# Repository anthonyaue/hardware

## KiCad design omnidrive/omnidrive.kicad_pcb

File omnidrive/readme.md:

List of components for digikey at https://www.digikey.com/en/mylists/list/IZ52OHNOLU

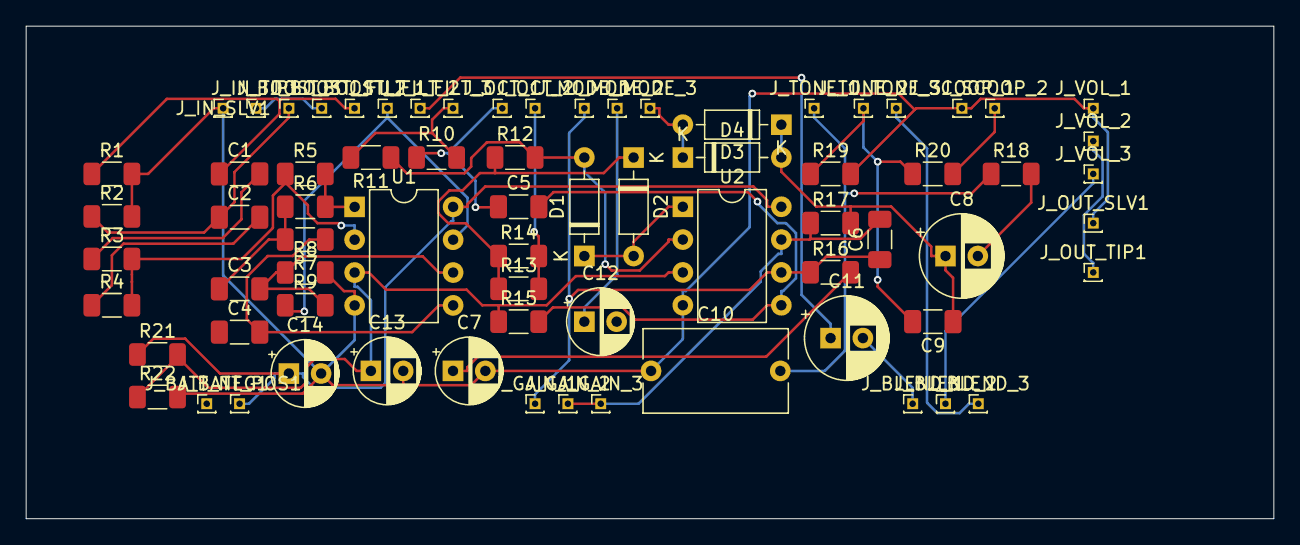
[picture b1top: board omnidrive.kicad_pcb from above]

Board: 2 copper layers, 96.5 x 38.1 mm, 73 parts (0 on the bottom side), 36 nets.

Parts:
C1, C5: 0.01uF; C_1206_3216Metric_Pad1.33x1.80mm_HandSolder
C2, C3, C4: 0.001uF; C_1206_3216Metric_Pad1.33x1.80mm_HandSolder
C6: 47pF; C_1206_3216Metric_Pad1.33x1.80mm_HandSolder
C7, C12, C13, C14: 10uF; CP_Radial_D5.0mm_P2.50mm
C8, C11: 1uF; CP_Radial_D6.3mm_P2.50mm
C9: 0.047uF; C_1206_3216Metric_Pad1.33x1.80mm_HandSolder
C10: 0.1uF; C_Rect_L11.0mm_W6.3mm_P10.00mm_MKT
D1, D2, D3, D4: 1N914; D_DO-35_SOD27_P7.62mm_Horizontal
J_BATT_NEG1: Conn_01x01_Pin; PinHeader_1x01_P1.00mm_Vertical
J_BATT_POS1: Conn_01x01_Pin; PinHeader_1x01_P1.00mm_Vertical
J_BLEND_1, J_BLEND_2, J_BLEND_3: Conn_01x01_Pin; PinHeader_1x01_P1.00mm_Vertical
J_BOOST_1, J_BOOST_2, J_BOOST_3: Conn_01x01_Pin; PinHeader_1x01_P1.00mm_Vertical
J_FILT_1, J_FILT_2, J_FILT_3: Conn_01x01_Pin; PinHeader_1x01_P1.00mm_Vertical
J_GAIN_1, J_GAIN_2, J_GAIN_3: Conn_01x01_Pin; PinHeader_1x01_P1.00mm_Vertical
J_IN_SLV1: Conn_01x01_Pin; PinHeader_1x01_P1.00mm_Vertical
J_IN_TIP1: Conn_01x01_Pin; PinHeader_1x01_P1.00mm_Vertical
J_MODE_1, J_MODE_2, J_MODE_3: Conn_01x01_Pin; PinHeader_1x01_P1.00mm_Vertical
J_OCT_1, J_OCT_2: Conn_01x01_Pin; PinHeader_1x01_P1.00mm_Vertical
J_OUT_SLV1: Conn_01x01_Pin; PinHeader_1x01_P1.00mm_Vertical
J_OUT_TIP1: Conn_01x01_Pin; PinHeader_1x01_P1.00mm_Vertical
J_SCOOP_1, J_SCOOP_2: Conn_01x01_Pin; PinHeader_1x01_P1.00mm_Vertical
J_TONE_1, J_TONE_2, J_TONE_3: Conn_01x01_Pin; PinHeader_1x01_P1.00mm_Vertical
J_VOL_1, J_VOL_2, J_VOL_3: Conn_01x01_Pin; PinHeader_1x01_P1.00mm_Vertical
R1, R2: 10M; R_1206_3216Metric_Pad1.30x1.75mm_HandSolder
R3: 330K; R_1206_3216Metric_Pad1.30x1.75mm_HandSolder
R4, R8, R9, R15: 100K; R_1206_3216Metric_Pad1.30x1.75mm_HandSolder
R5: 1M; R_1206_3216Metric_Pad1.30x1.75mm_HandSolder
R6, R7: 220K; R_1206_3216Metric_Pad1.30x1.75mm_HandSolder
R10, R11, R12, R13, R14, R19, R21, R22: 10K; R_1206_3216Metric_Pad1.30x1.75mm_HandSolder
R16, R17, R20: 1K; R_1206_3216Metric_Pad1.30x1.75mm_HandSolder
R18: 3.9K; R_1206_3216Metric_Pad1.30x1.75mm_HandSolder
U1, U2: TL072; DIP-8_W7.62mm

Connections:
+9V: C14.1, J_BATT_POS1.1, R21.1, U1.8 (V+), U2.8 (V+)
/Vb: C13.1, R15.1, R21.2, R22.1, U1.3 (+), U2.3 (+)
GND: C7.2, C10.1, C13.2, C14.2, J_IN_SLV1.1, J_OUT_SLV1.1, J_SCOOP_1.1, J_VOL_1.1, R1.2, R2.2, R8.2, R19.2, R22.2, U1.4 (V-), U2.4 (V-)
unnamed: C1.2, R3.1
unnamed: C2.2, R4.1
unnamed: C3.1, R6.1, R7.2
unnamed: C7.1, R16.2
unnamed: C8.2, R18.2
unnamed: D1.2 (A), R11.1, R12.2, U2.2 (-)
unnamed: D1.1 (K), D2.2 (A), U2.1
unnamed: D2.1 (K), R12.1, R13.1, R14.1
unnamed: D3.2 (A), D4.1 (K), J_MODE_3.1
unnamed: C8.1, C9.1, D3.1 (K), D4.2 (A), R17.2
unnamed: C11.2, J_BLEND_1.1
unnamed: J_BLEND_2.1, J_VOL_3.1
unnamed: J_BLEND_3.1, J_TONE_3.1
unnamed: J_BOOST_1.1, J_IN_TIP1.1
unnamed: C1.1, J_BOOST_2.1, R1.1
unnamed: C2.1, J_BOOST_3.1, R2.1
unnamed: J_FILT_1.1, R9.1, U1.7
unnamed: C11.1, J_FILT_2.1
unnamed: J_FILT_3.1, R10.2, R11.2
unnamed: C6.1, J_GAIN_1.1, J_MODE_1.1, R16.1, U2.6 (-)
unnamed: C6.2, J_GAIN_2.1, J_GAIN_3.1, R17.1, U2.7
unnamed: C12.1, J_MODE_2.1
unnamed: C5.1, J_OCT_1.1, R10.1
unnamed: J_OCT_2.1, R13.2, R14.2
unnamed: J_OUT_TIP1.1, J_VOL_2.1
unnamed: J_SCOOP_2.1, R20.2
unnamed: C10.2, J_TONE_1.1, R18.1
unnamed: C9.2, J_TONE_2.1, R19.1, R20.1
unnamed: R5.2, R6.2, U1.1
unnamed: R3.2, R4.2, R5.1, U1.2 (-)
unnamed: C4.2, R7.1, U1.5 (+)
unnamed: C3.2, R8.1, R9.2, U1.6 (-)
unnamed: C5.2, R15.2, U2.5 (+)

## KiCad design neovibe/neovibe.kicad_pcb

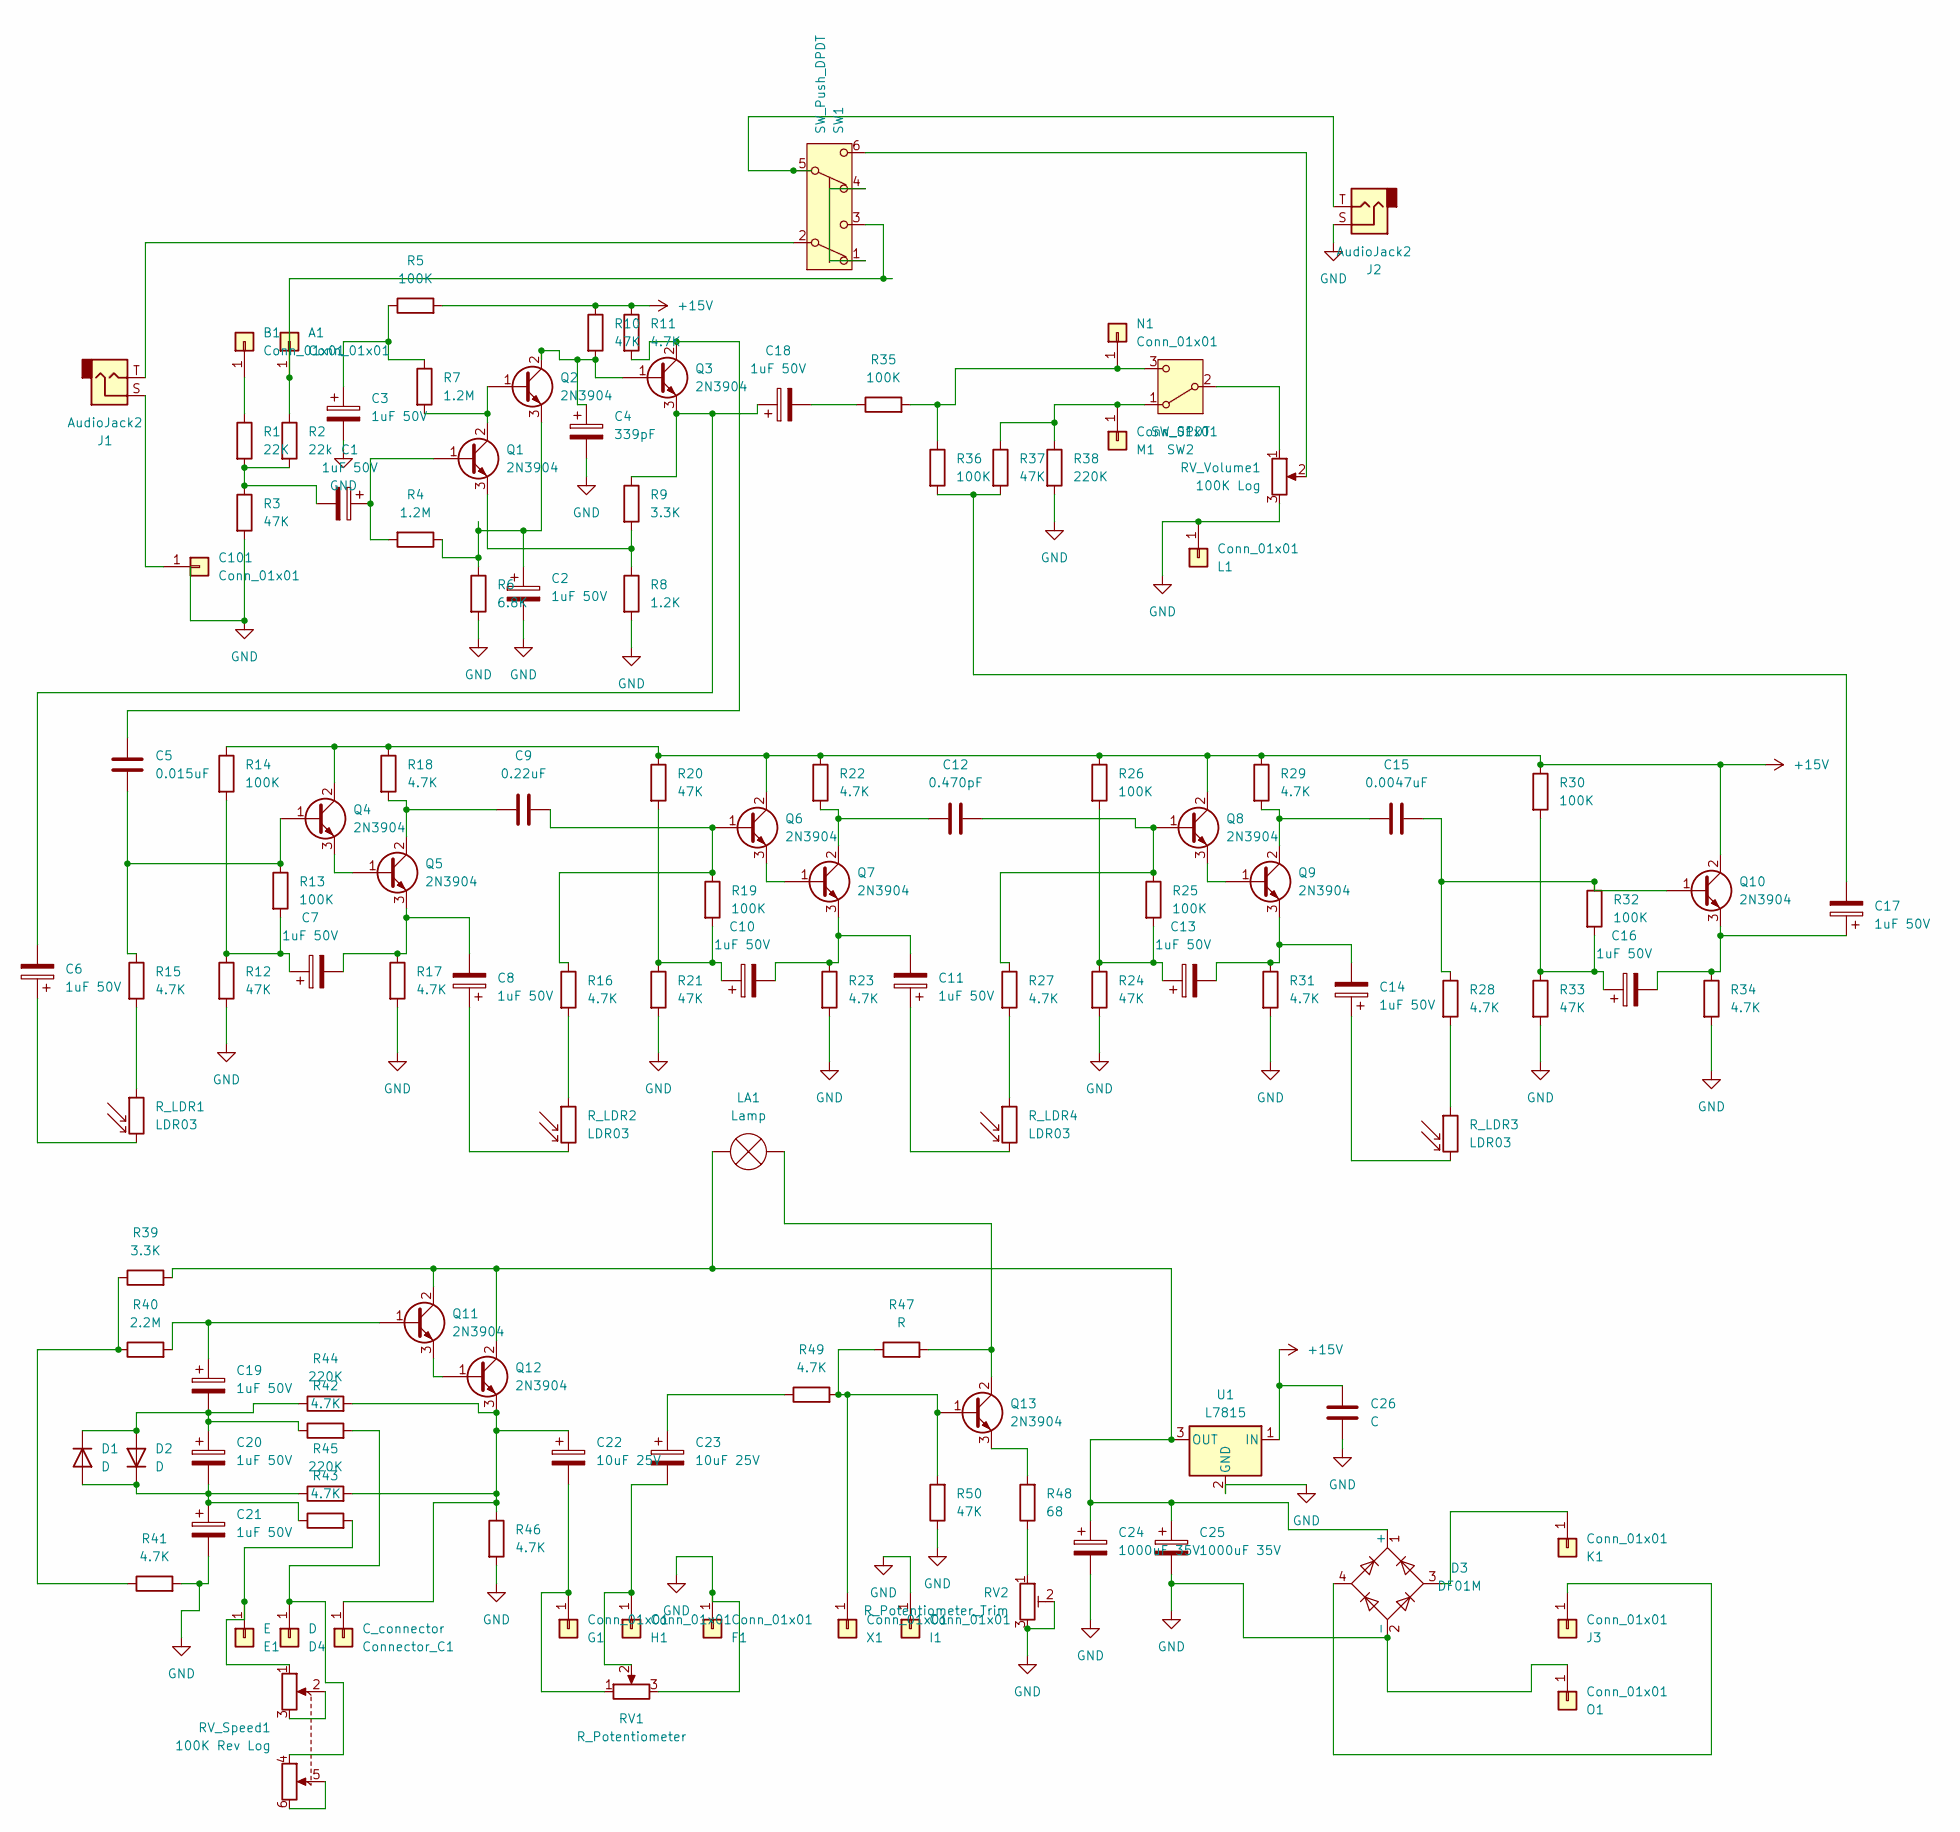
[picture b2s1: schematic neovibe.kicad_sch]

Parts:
A1: Conn_01x01; PinHeader_1x01_P1.00mm_Vertical
B1: Conn_01x01; PinHeader_1x01_P1.00mm_Vertical
C1, C2, C3, C6, C7, C8, C10, C11, C13, C14, C16, C17, C18, C19, C20, C21: 1uF 50V; CP_Radial_D6.3mm_P2.50mm
C4: 339pF; C_Axial_L12.0mm_D6.5mm_P15.00mm_Horizontal
C5: 0.015uF; CP_Radial_D6.3mm_P2.50mm
C9: 0.22uF; C_Rect_L10.3mm_W5.7mm_P7.50mm_MKS4
C12: 0.470pF; C_Rect_L7.2mm_W4.5mm_P5.00mm_FKS2_FKP2_MKS2_MKP2
C15: 0.0047uF; C_Rect_L7.2mm_W2.5mm_P5.00mm_FKS2_FKP2_MKS2_MKP2
C22, C23: 10uF 25V; CP_Radial_D5.0mm_P2.50mm
C24, C25: 1000uF 35V; CP_Radial_D12.5mm_P5.00mm
C26: C; C_Disc_D12.5mm_W5.0mm_P7.50mm
C101: Conn_01x01; PinHeader_1x01_P1.00mm_Vertical
Connector_C1: C_connector; PinHeader_1x01_P1.00mm_Vertical
D1, D2: D; D_DO-35_SOD27_P3.81mm_Vertical_AnodeUp
D3: DF01M; Diode_Bridge_DIP-4_W7.62mm_P5.08mm
D4: D; PinHeader_1x01_P1.00mm_Vertical
E1: E; PinHeader_1x01_P1.00mm_Vertical
F1: Conn_01x01; PinHeader_1x01_P1.00mm_Vertical
G1: Conn_01x01; PinHeader_1x01_P1.00mm_Vertical
H1: Conn_01x01; PinHeader_1x01_P1.00mm_Vertical
I1: Conn_01x01; PinHeader_1x01_P1.00mm_Vertical
J1, J2: AudioJack2
J3: Conn_01x01; PinHeader_1x01_P1.00mm_Vertical
K1: Conn_01x01; PinHeader_1x01_P1.00mm_Vertical
L1: Conn_01x01; PinHeader_1x01_P1.00mm_Vertical
LA1: Lamp; PinHeader_1x02_P1.27mm_Vertical
M1: Conn_01x01; PinHeader_1x01_P1.00mm_Vertical
N1: Conn_01x01; PinHeader_1x01_P1.00mm_Vertical
O1: Conn_01x01; PinHeader_1x01_P1.00mm_Vertical
Q1, Q2, Q3, Q4, Q5, Q6, Q7, Q8, Q9, Q10, Q11, Q12, Q13: 2N3904; TO-92L_HandSolder
R1: 22K; R_Axial_DIN0207_L6.3mm_D2.5mm_P7.62mm_Horizontal
R2: 22k; R_Axial_DIN0207_L6.3mm_D2.5mm_P7.62mm_Horizontal
R3, R10, R12, R20, R21, R24, R33, R37, R50: 47K; R_Axial_DIN0204_L3.6mm_D1.6mm_P5.08mm_Horizontal
R4, R7: 1.2M; R_Axial_DIN0207_L6.3mm_D2.5mm_P7.62mm_Horizontal
R5, R13, R14, R19, R25, R26, R30, R32, R35, R36: 100K; R_Axial_DIN0207_L6.3mm_D2.5mm_P7.62mm_Horizontal
R6: 6.8K; R_Axial_DIN0207_L6.3mm_D2.5mm_P7.62mm_Horizontal
R8: 1.2K; R_Axial_DIN0207_L6.3mm_D2.5mm_P7.62mm_Horizontal
R9, R39: 3.3K; R_Box_L8.4mm_W2.5mm_P5.08mm
R11, R15, R16, R17, R18, R22, R23, R27, R28, R29, R31, R34, R41, R42, R43, R46, R49: 4.7K; R_Axial_DIN0207_L6.3mm_D2.5mm_P7.62mm_Horizontal
R38, R44, R45: 220K; R_Axial_DIN0207_L6.3mm_D2.5mm_P7.62mm_Horizontal
R40: 2.2M; R_Axial_DIN0207_L6.3mm_D2.5mm_P7.62mm_Horizontal
R47: R; R_Axial_DIN0207_L6.3mm_D2.5mm_P7.62mm_Horizontal
R48: 68; R_Axial_DIN0309_L9.0mm_D3.2mm_P12.70mm_Horizontal
RV1: R_Potentiometer
RV2: R_Potentiometer_Trim; Potentiometer_Vishay_148-149_Single_Vertical
RV_Speed1: 100K Rev Log
RV_Volume1: 100K Log
R_LDR1, R_LDR2, R_LDR3, R_LDR4: LDR03; R_LDR_10x8.5mm_P7.6mm_Vertical
SW1: SW_Push_DPDT
SW2: SW_SPDT
U1: L7815; TO-220-3_Vertical
X1: Conn_01x01; PinHeader_1x01_P1.00mm_Vertical

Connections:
+15V: C26.1, Q4.2 (C), Q6.2 (C), Q8.2 (C), Q10.2 (C), R5.2, R10.1, R11.1, R14.1, R18.1, R20.1, R22.1, R26.1, R29.1, R30.1, U1.1 (IN)
GND: C2.2, C3.2, C4.2, C21.2, C24.2, C25.2, C26.2, D3.2 (-), F1.1, I1.1, J2.S, L1.1, O1.1, R3.2, R6.2, R8.2, R12.2, R17.2, R21.2, R23.2, R24.2, R31.2, R33.2, R34.2, R38.2, R41.2, R46.2, R50.1, RV1.3, RV2.2, RV2.3, RV_Volume1.3, U1.2 (GND)
unnamed: A1.1, R2.1, SW1.3 (C)
unnamed: B1.1, R1.1
unnamed: C1.2, R1.2, R2.2, R3.1
unnamed: C3.1, R5.1, R7.1
unnamed: C6.1, R_LDR1.2
unnamed: C7.1, R12.1, R13.2, R14.2
unnamed: C8.1, R_LDR2.2
unnamed: C10.1, R19.2, R20.2, R21.1
unnamed: C11.1, R_LDR4.2
unnamed: C13.1, R24.1, R25.2, R26.2
unnamed: C14.1, R_LDR3.2
unnamed: C16.1, R30.2, R32.2, R33.1
unnamed: C17.2, R36.2, R37.2
unnamed: C18.2, R35.1
unnamed: C23.1, R49.1
unnamed: C101.1, J1.S
unnamed: C22.1, Connector_C1.1, Q12.3 (E), R44.2, R45.2, R46.1
unnamed: C20.2, C21.1, D1.2 (A), D2.1 (K), R43.1, R45.1
unnamed: C19.2, C20.1, D1.1 (K), D2.2 (A), R42.1, R44.1
unnamed: C24.1, C25.1, D3.1 (+), LA1.2 (+), Q11.2 (C), Q12.2 (C), R39.2, U1.3 (OUT)
unnamed: D4.1, R42.2, RV_Speed1.4
unnamed: E1.1, R43.2, RV_Speed1.1
unnamed: C22.2, G1.1, RV1.1
unnamed: C23.2, H1.1, RV1.2
unnamed: J1.T, SW1.2 (B)
unnamed: J2.T, SW1.5 (B)
unnamed: D3.4, J3.1
unnamed: D3.3, K1.1
unnamed: LA1.1 (-), Q13.2 (C), R47.2
unnamed: M1.1, R37.1, R38.1, SW2.1 (A)
unnamed: N1.1, R35.2, R36.1, SW2.3 (C)
unnamed: C1.1, Q1.1 (B), R4.2
unnamed: Q1.2 (C), Q2.1 (B), R7.2
unnamed: Q1.3 (E), R8.1, R9.2
unnamed: C4.1, Q2.2 (C), Q3.1 (B), R10.2
unnamed: C2.1, Q2.3 (E), R4.1, R6.1
unnamed: C5.1, Q3.2 (C), R11.2
unnamed: C6.2, C18.1, Q3.3 (E), R9.1
unnamed: C5.2, Q4.1 (B), R13.1, R15.1
unnamed: Q4.3 (E), Q5.1 (B)
unnamed: C9.1, Q5.2 (C), R18.2
unnamed: C7.2, C8.2, Q5.3 (E), R17.1
unnamed: C9.2, Q6.1 (B), R16.1, R19.1
unnamed: Q6.3 (E), Q7.1 (B)
unnamed: C12.1, Q7.2 (C), R22.2
unnamed: C10.2, C11.2, Q7.3 (E), R23.1
unnamed: C12.2, Q8.1 (B), R25.1, R27.1
unnamed: Q8.3 (E), Q9.1 (B)
unnamed: C15.1, Q9.2 (C), R29.2
unnamed: C13.2, C14.2, Q9.3 (E), R31.1
unnamed: C15.2, Q10.1 (B), R28.1, R32.1
unnamed: C16.2, C17.1, Q10.3 (E), R34.1
unnamed: C19.1, Q11.1 (B), R40.2
unnamed: Q11.3 (E), Q12.1 (B)
unnamed: Q13.1 (B), R47.1, R49.2, R50.2, X1.1
unnamed: Q13.3 (E), R48.2
unnamed: R15.2, R_LDR1.1
unnamed: R16.2, R_LDR2.1
unnamed: R27.2, R_LDR4.1
unnamed: R28.2, R_LDR3.1
unnamed: R39.1, R40.1, R41.1
unnamed: R48.1, RV2.1
unnamed: RV_Speed1.2, RV_Speed1.3
unnamed: RV_Speed1.5, RV_Speed1.6
unnamed: RV_Volume1.1, SW2.2 (B)
unnamed: RV_Volume1.2, SW1.6 (C)
unnamed: SW1.1 (A), SW1.4 (A)

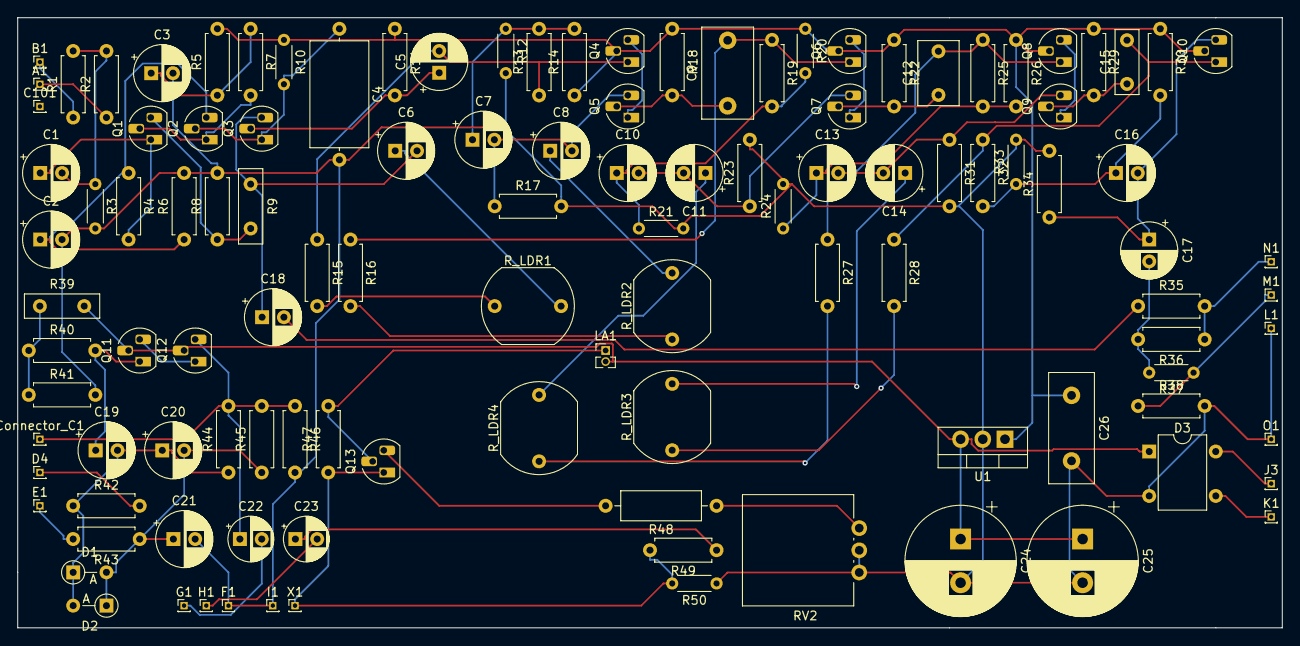
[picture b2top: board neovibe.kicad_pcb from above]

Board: 2 copper layers, 144.8 x 69.8 mm, 116 parts (0 on the bottom side), 61 nets.

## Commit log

2024-02-19 start
2024-02-19 Added power section
2024-02-19 Finished circuit
2024-02-20 bunchastuff
2025-05-17 neovibe
2025-05-18 stuff
2025-05-18 fix ec
2025-05-19 footprints
2025-05-19 begin layout
2025-05-19 more placement
2025-05-20 2 layer autorouted
2025-05-23 first omni schematic
2025-05-23 annotation and ERC check
2025-05-23 offboarding
2025-05-24 assigned footprints
2025-05-24 start placement
2025-05-24 add link to digikey list
2025-05-24 more placement, attach output jack
2025-05-24 fix some cnxs and place everything
2025-05-24 some routing but not complete
